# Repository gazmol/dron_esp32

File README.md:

# dron_esp32
 drone with esp32 super mini c3

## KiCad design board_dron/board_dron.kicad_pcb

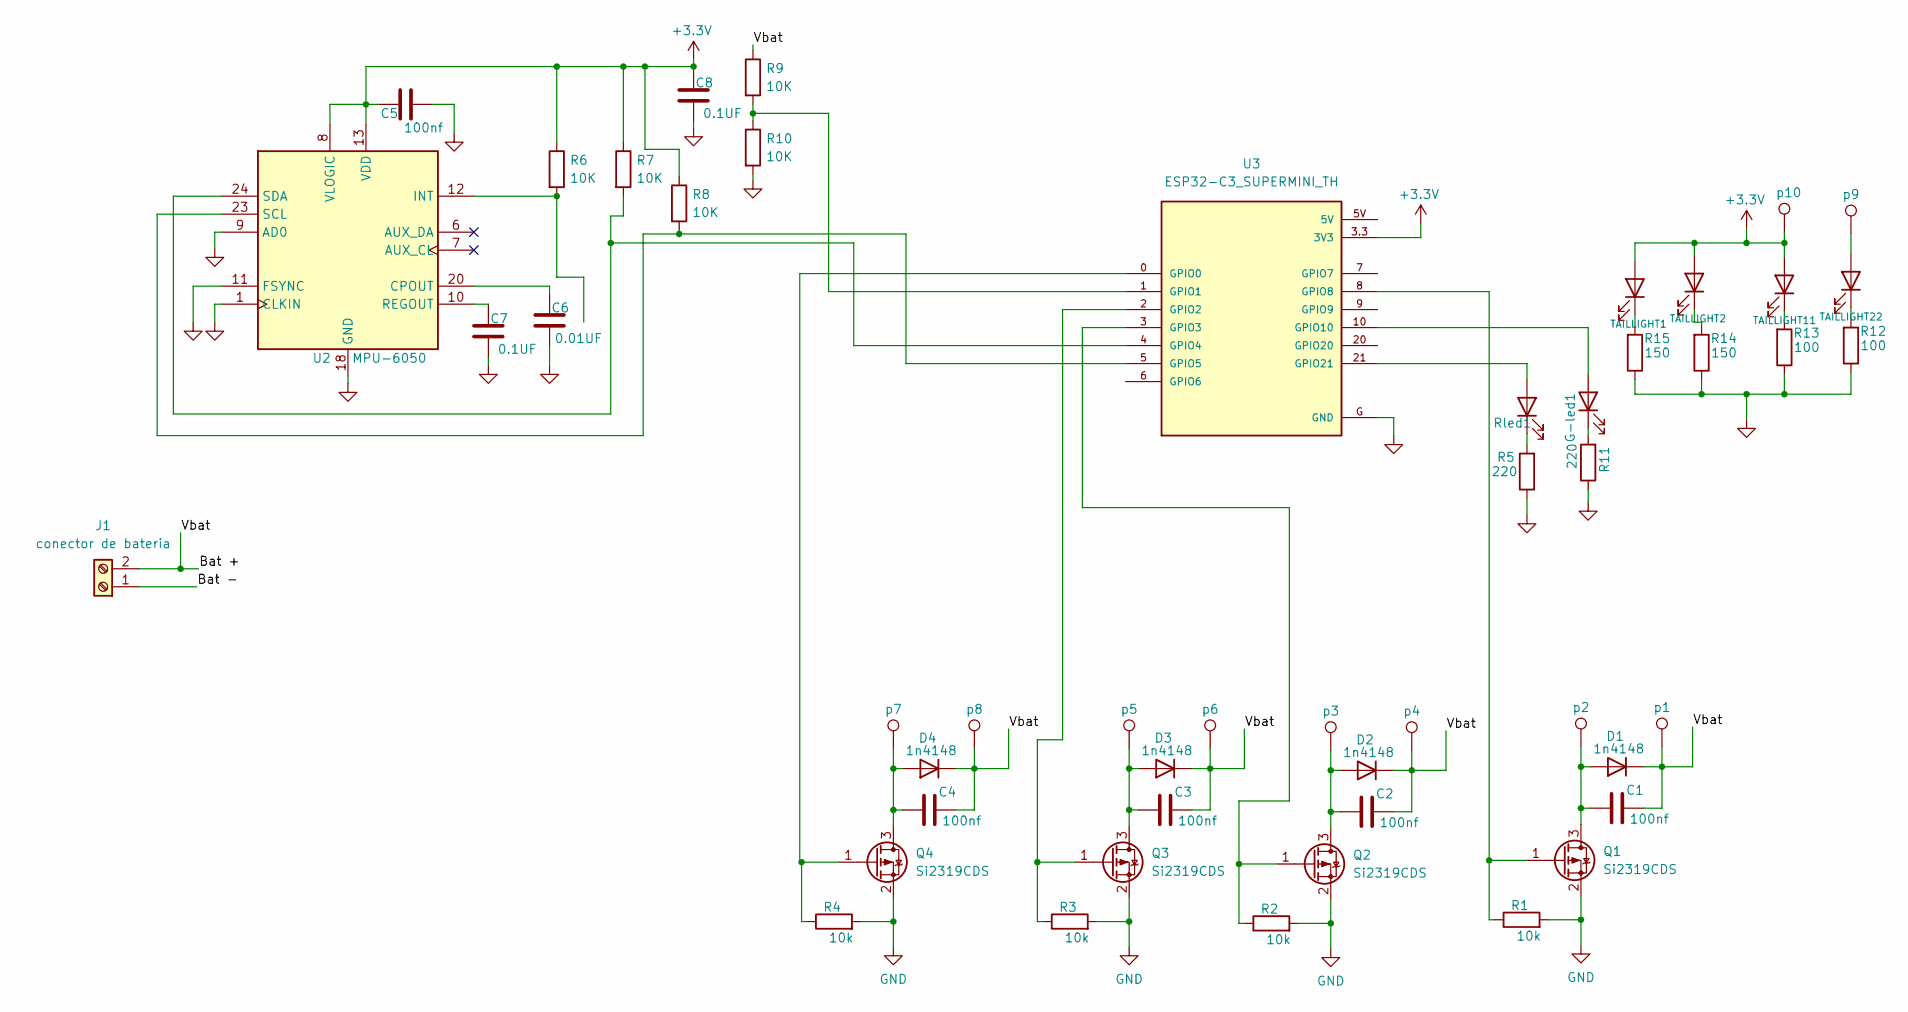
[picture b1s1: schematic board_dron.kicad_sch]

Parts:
C1, C2, C3, C4, C5: 100nf; C_0201_0603Metric
C6: 0.01UF; C_0201_0603Metric
C7, C8: 0.1UF; C_0201_0603Metric
D1, D2, D3, D4: 1n4148; D_A-405_P7.62mm_Horizontal
G-led1: LED; LED_0201_0603Metric
J1: conector de bateria; TerminalBlock_bornier-2_P5.08mm
Q1, Q2, Q3, Q4: Si2319CDS; SOT-23
R1, R2, R3, R4: 10k; R_0201_0603Metric_Pad0.64x0.40mm_HandSolder
R5, R11: 220; R_0201_0603Metric_Pad0.64x0.40mm_HandSolder
R6, R7, R8, R9, R10: 10K; R_0201_0603Metric_Pad0.64x0.40mm_HandSolder
R12, R13: 100; R_0201_0603Metric_Pad0.64x0.40mm_HandSolder
R14, R15: 150; R_0201_0603Metric_Pad0.64x0.40mm_HandSolder
Rled1: LED; LED_0201_0603Metric
TAILLIGHT1, TAILLIGHT2, TAILLIGHT11, TAILLIGHT22: LED; LED_0201_0603Metric
U2: MPU-6050; InvenSense_QFN-24_4x4mm_P0.5mm
U3: ESP32-C3_SUPERMINI_TH; MODULE_ESP32-C3_SUPERMINI
p1, p2, p3, p4, p5, p6, p7, p8, p9, p10: TestPoint; Pin_D1.1mm_L10.2mm_W3.5mm_Flat

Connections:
+3.3V: C5.1, C8.2, R6.1, R7.1, R8.1, TAILLIGHT1.2 (A), TAILLIGHT2.2 (A), TAILLIGHT11.2 (A), U2.8 (VLOGIC), U2.13 (VDD), U3.3.3 (3V3), p10.1
/Bat +: C1.2, C2.2, C3.2, C4.2, D1.1 (K), D2.1 (K), D3.1 (K), D4.1 (K), J1.2, R9.1, p1.1, p4.1, p6.1, p8.1
/Bat -: J1.1
GND: C5.2, C6.1, C7.1, C8.1, Q1.2 (S), Q2.2 (S), Q3.2 (S), Q4.2 (S), R1.2, R2.2, R3.2, R4.2, R5.1, R10.2, R11.1, R12.1, R13.1, R14.1, R15.1, U2.1 (CLKIN), U2.9 (AD0), U2.11 (FSYNC), U2.18 (GND), U3.G (GND)
unnamed: C1.1, D1.2 (A), Q1.3 (D), p2.1
unnamed: C2.1, D2.2 (A), Q2.3 (D), p3.1
unnamed: C3.1, D3.2 (A), Q3.3 (D), p5.1
unnamed: C4.1, D4.2 (A), Q4.3 (D), p7.1
unnamed: G-led1.2 (A), U3.10 (GPIO10)
unnamed: G-led1.1 (K), R11.2
unnamed: Q1.1 (G), R1.1, U3.8 (GPIO8)
unnamed: Q2.1 (G), R2.1, U3.3 (GPIO3)
unnamed: Q3.1 (G), R3.1, U3.2 (GPIO2)
unnamed: Q4.1 (G), R4.1, U3.0 (GPIO0)
unnamed: Rled1.2 (A), U3.21 (GPIO21)
unnamed: R5.2, Rled1.1 (K)
unnamed: R15.2, TAILLIGHT1.1 (K)
unnamed: R14.2, TAILLIGHT2.1 (K)
unnamed: R13.2, TAILLIGHT11.1 (K)
unnamed: TAILLIGHT22.2 (A), p9.1
unnamed: R12.2, TAILLIGHT22.1 (K)
unnamed: C6.2, U2.20 (CPOUT)
unnamed: R6.2, U2.12 (INT)
unnamed: C7.2, U2.10 (REGOUT)
unnamed: R8.2, U2.23 (SCL), U3.5 (GPIO5)
unnamed: R7.2, U2.24 (SDA), U3.4 (GPIO4)
unnamed: R9.2, R10.1, U3.1 (GPIO1)

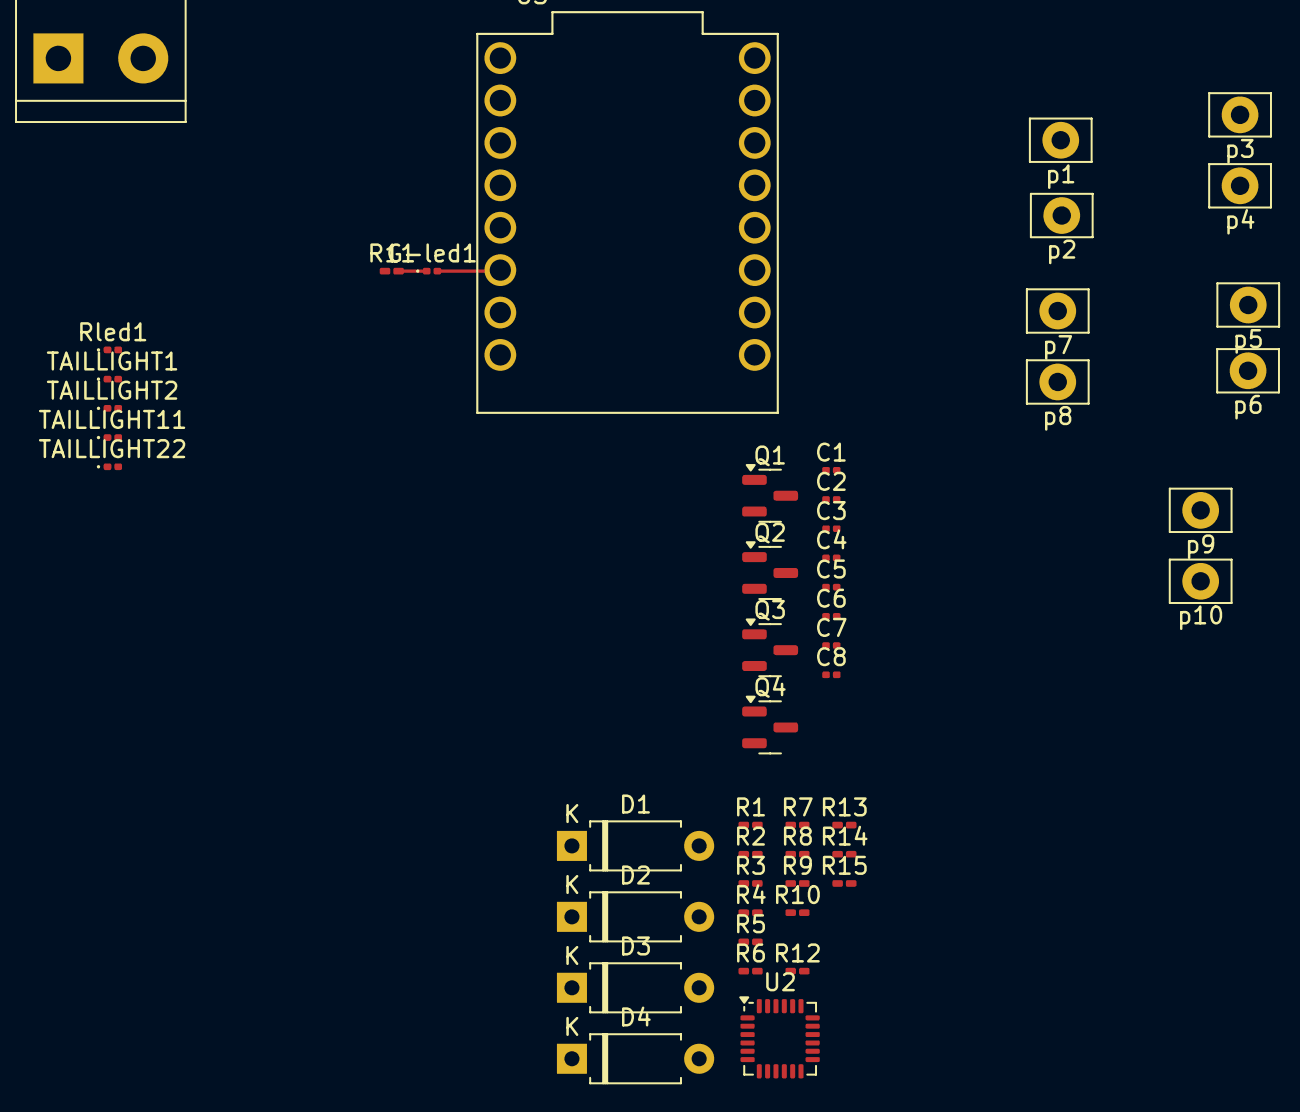
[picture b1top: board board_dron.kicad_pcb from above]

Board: 2 copper layers, 50 parts (0 on the bottom side), 26 nets.
